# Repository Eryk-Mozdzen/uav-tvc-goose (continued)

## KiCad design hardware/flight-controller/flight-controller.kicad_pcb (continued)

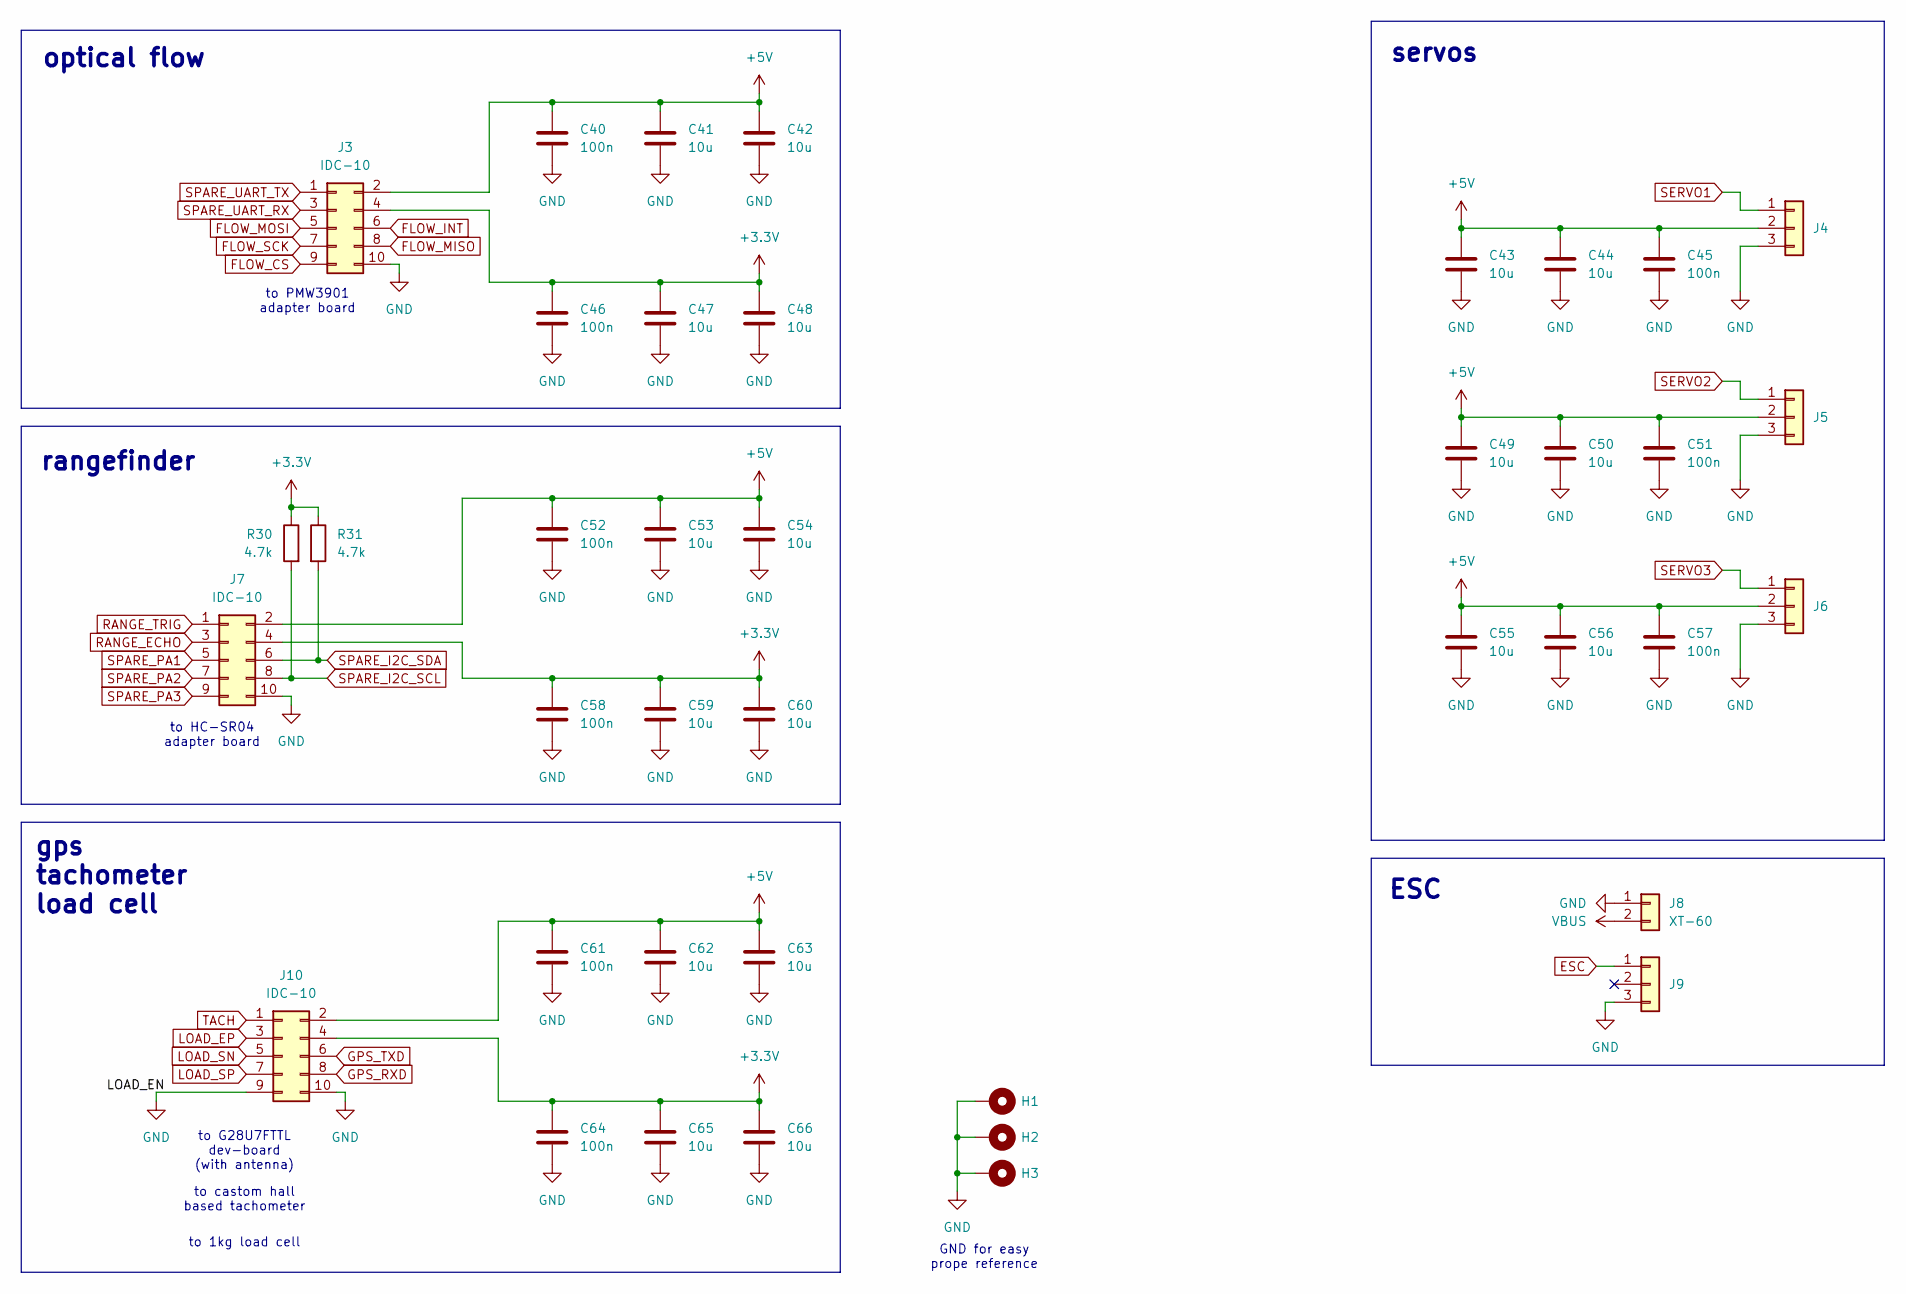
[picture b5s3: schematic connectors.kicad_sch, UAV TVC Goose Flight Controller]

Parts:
C40, C45, C46, C51, C52, C57, C58, C61, C64: 100n; C_0603_1608Metric
C41, C42, C43, C44, C47, C48, C49, C50, C53, C54, C55, C56, C59, C60, C62, C63, C65, C66: 10u; C_0603_1608Metric
H1, H2, H3: MountingHole_Pad; MountingHole_3.5mm_Pad_Via
J3, J7, J10: IDC-10; IDC-10-horizontal
J4, J5, J6, J9: Conn_01x03; header_1x3
J8: XT-60; XT60PW-F
R30, R31: 4.7k; R_0603_1608Metric

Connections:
+3.3V: C46.1, C47.1, C48.1, C58.1, C59.1, C60.1, C64.1, C65.1, C66.1, J3.4, J7.4, J10.4, R30.1, R31.1; also elsewhere on the board
+5V: C40.1, C41.1, C42.1, C43.1, C44.1, C45.1, C49.1, C50.1, C51.1, C52.1, C53.1, C54.1, C55.1, C56.1, C57.1, C61.1, C62.1, C63.1, J3.2, J4.2, J5.2, J6.2, J7.2, J10.2; also elsewhere on the board
ESC: J9.1; also elsewhere on the board
FLOW_CS: J3.9; also elsewhere on the board
FLOW_INT: J3.6; also elsewhere on the board
FLOW_MISO: J3.8; also elsewhere on the board
FLOW_MOSI: J3.5; also elsewhere on the board
FLOW_SCK: J3.7; also elsewhere on the board
GND: C40.2, C41.2, C42.2, C43.2, C44.2, C45.2, C46.2, C47.2, C48.2, C49.2, C50.2, C51.2, C52.2, C53.2, C54.2, C55.2, C56.2, C57.2, C58.2, C59.2, C60.2, C61.2, C62.2, C63.2, C64.2, C65.2, C66.2, H1.1, H2.1, H3.1, J3.10, J4.3, J5.3, J6.3, J7.10, J8.1, J9.3, J10.9, J10.10; also elsewhere on the board
GPS_RXD: J10.8; also elsewhere on the board
GPS_TXD: J10.6; also elsewhere on the board
LOAD_EP: J10.3; also elsewhere on the board
LOAD_SN: J10.5; also elsewhere on the board
LOAD_SP: J10.7; also elsewhere on the board
RANGE_ECHO: J7.3; also elsewhere on the board
RANGE_TRIG: J7.1; also elsewhere on the board
SERVO1: J4.1; also elsewhere on the board
SERVO2: J5.1; also elsewhere on the board
SERVO3: J6.1; also elsewhere on the board
SPARE_I2C_SCL: J7.8, R30.2; also elsewhere on the board
SPARE_I2C_SDA: J7.6, R31.2; also elsewhere on the board
SPARE_PA1: J7.5; also elsewhere on the board
SPARE_PA2: J7.7; also elsewhere on the board
SPARE_PA3: J7.9; also elsewhere on the board
SPARE_UART_RX: J3.3; also elsewhere on the board
SPARE_UART_TX: J3.1; also elsewhere on the board
TACH: J10.1; also elsewhere on the board
VBUS: J8.2; also elsewhere on the board

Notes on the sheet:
to HC-SR04 adapter board
to PMW3901 adapter board
to 1kg load cell
GND for easy prope reference
optical flow
ESC
to castom hall based tachometer
gps tachometer load cell
servos
rangefinder
to G28U7FTTL dev-board (with antenna)

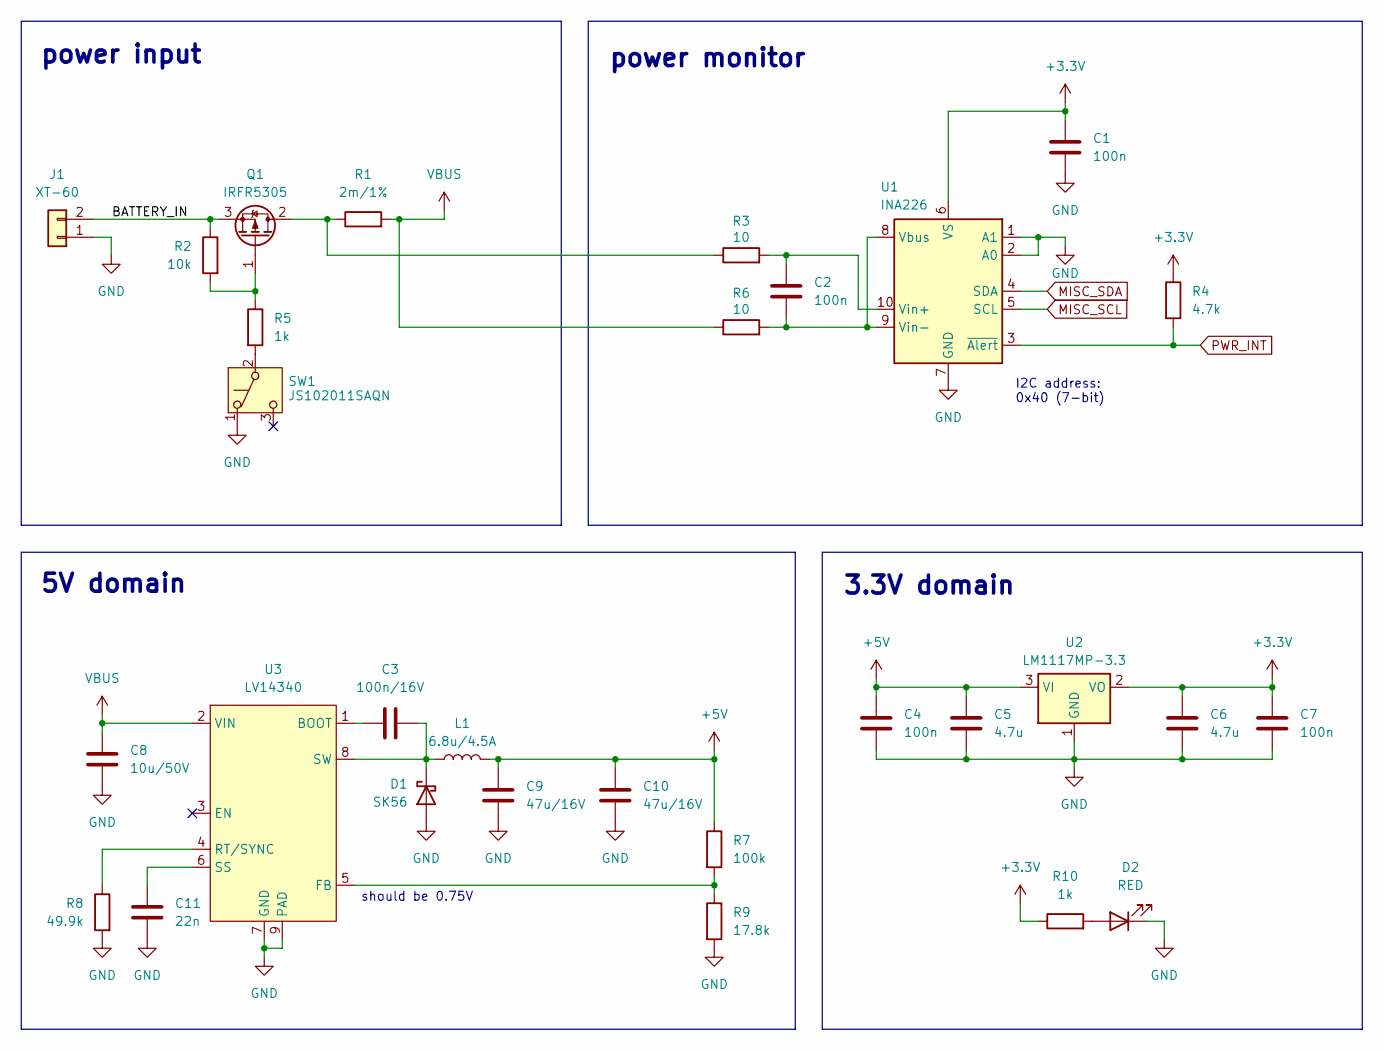
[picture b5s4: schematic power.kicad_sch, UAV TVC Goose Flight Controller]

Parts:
C1, C2, C4, C7: 100n; C_0603_1608Metric
C3: 100n/16V; C_0603_1608Metric
C5, C6: 4.7u; C_0603_1608Metric
C8: 10u/50V; C_1206_3216Metric
C9, C10: 47u/16V; C_1206_3216Metric
C11: 22n; C_0603_1608Metric
D1: SK56; D_SMB
D2: RED; LED_0603_1608Metric
J1: XT-60; XT60PW-M
L1: 6.8u/4.5A; PA4341.XXXNLT
Q1: IRFR5305; TO-252-2
R1: 2m/1%; R_1206_3216Metric
R2: 10k; R_0603_1608Metric
R3, R6: 10; R_0603_1608Metric
R4: 4.7k; R_0603_1608Metric
R5, R10: 1k; R_0603_1608Metric
R7: 100k; R_0603_1608Metric
R8: 49.9k; R_0603_1608Metric
R9: 17.8k; R_0603_1608Metric
SW1: JS102011SAQN
U1: INA226
U2: LM1117MP-3.3; LM1117-3.3
U3: LV14340

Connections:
+3.3V: C1.1, C6.1, C7.1, R4.1, R10.1, U1.6 (VS), U2.2 (VO); also elsewhere on the board
+5V: C4.1, C5.1, C9.1, C10.1, L1.2, R7.1, U2.3 (VI); also elsewhere on the board
/power/BATTERY_IN: J1.2, Q1.3 (S), R2.1
GND: C1.2, C4.2, C5.2, C6.2, C7.2, C8.2, C9.2, C10.2, C11.2, D1.2 (A), D2.1 (K), J1.1, R8.2, R9.2, SW1.1 (A), U1.1 (A1), U1.2 (A0), U1.7 (GND), U2.1 (GND), U3.7 (GND), U3.9 (PAD); also elsewhere on the board
MISC_SCL: U1.5 (SCL); also elsewhere on the board
MISC_SDA: U1.4 (SDA); also elsewhere on the board
unnamed: C3.2, D1.1 (K), L1.1, U3.8 (SW)
unnamed: D2.2 (A), R10.2
unnamed: Q1.2 (D), R1.1, R3.1
unnamed: Q1.1 (G), R2.2, R5.1
unnamed: R5.2, SW1.2 (B)
unnamed: C2.2, R6.2, U1.8 (Vbus), U1.9 (Vin-)
unnamed: C2.1, R3.2, U1.10 (Vin+)
unnamed: C3.1, U3.1 (BOOT)
unnamed: R7.2, R9.1, U3.5 (FB)
unnamed: R8.1, U3.4 (RT/SYNC)
unnamed: C11.1, U3.6 (SS)
PWR_INT: R4.2, U1.3 (~Alert); also elsewhere on the board
VBUS: C8.1, R1.2, R6.1, U3.2 (VIN); also elsewhere on the board

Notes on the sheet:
I2C address: 0x40 (7-bit)
5V domain
power monitor
should be 0.75V
3.3V domain
power input

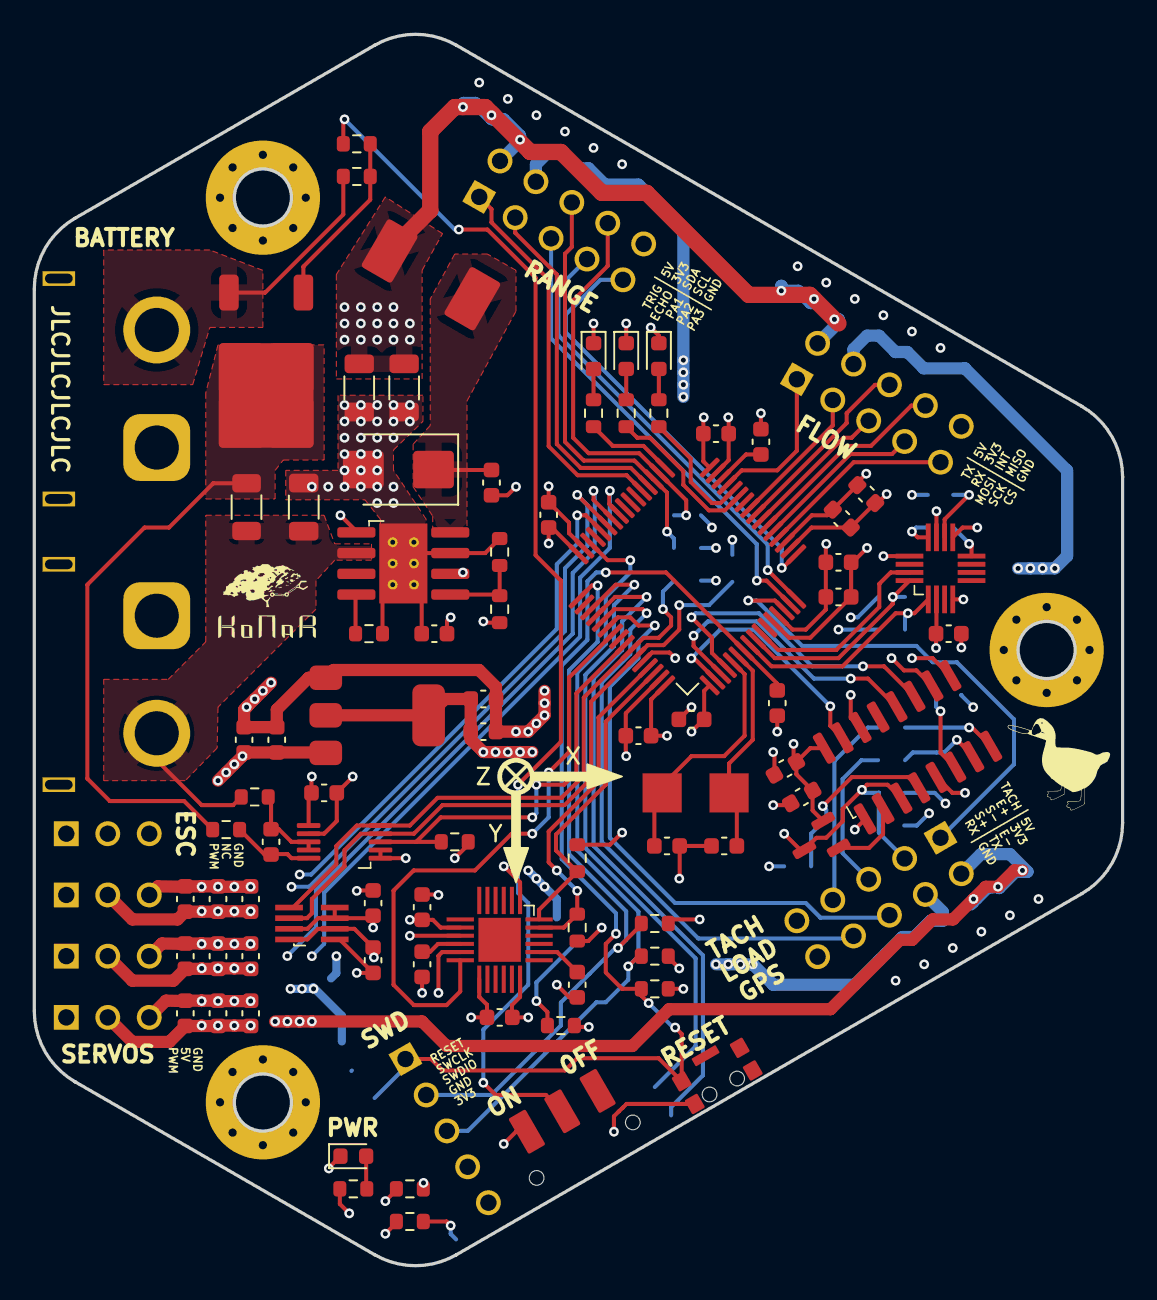
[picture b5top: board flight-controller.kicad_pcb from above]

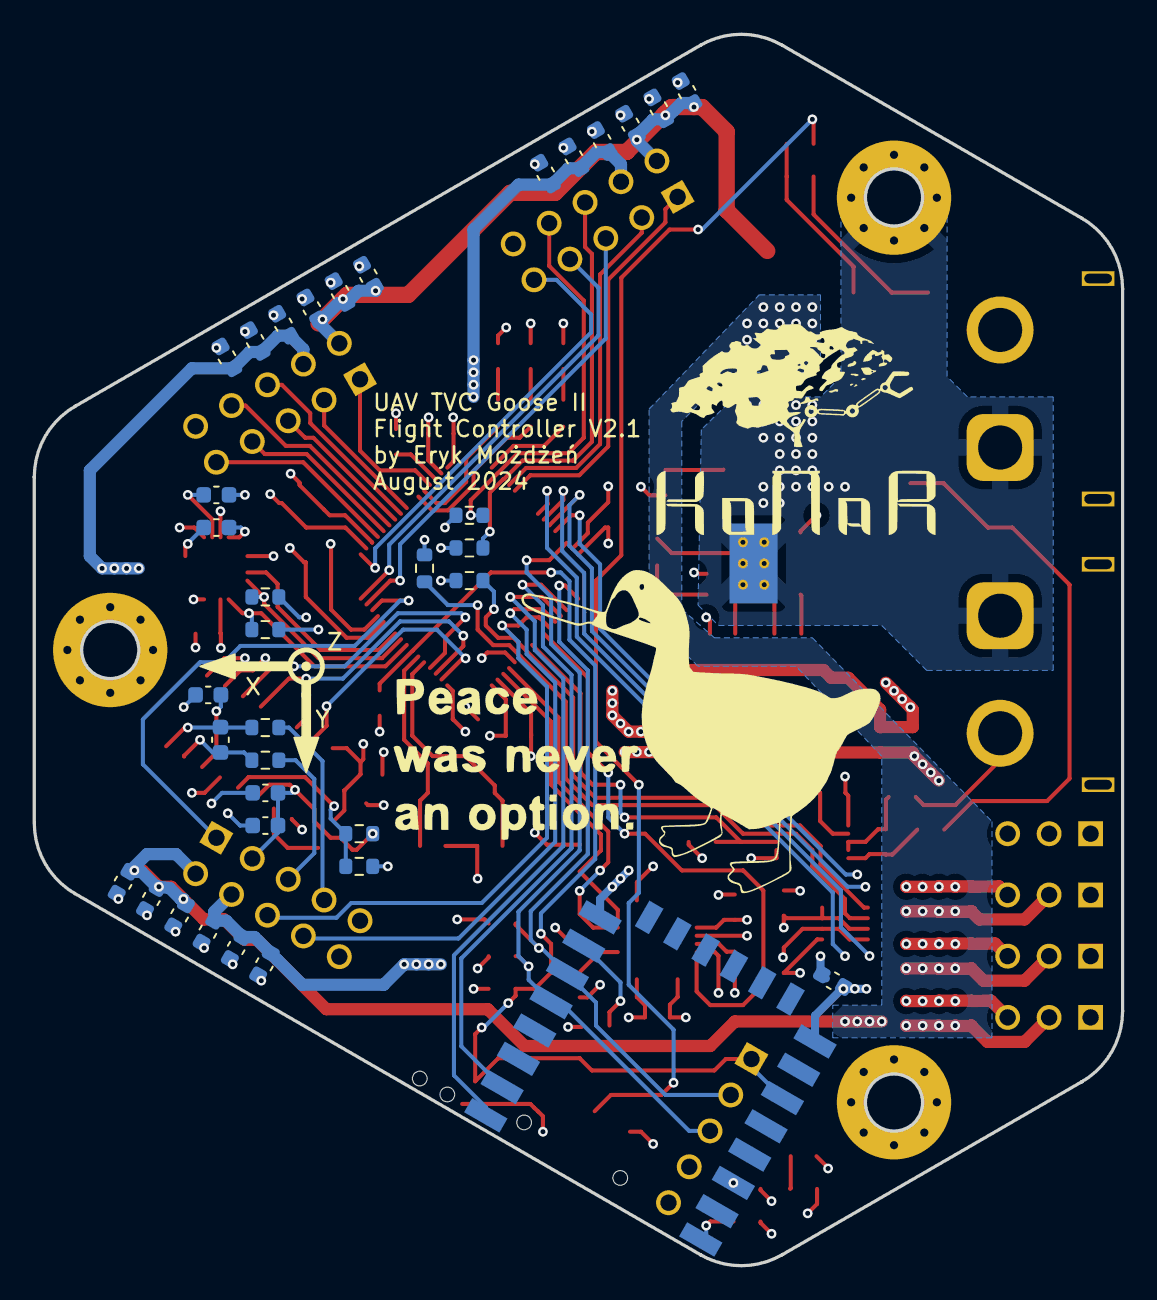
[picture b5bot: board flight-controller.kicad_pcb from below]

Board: 4 copper layers, 66.7 x 75.4 mm, 130 parts (36 on the bottom side), 79 nets.

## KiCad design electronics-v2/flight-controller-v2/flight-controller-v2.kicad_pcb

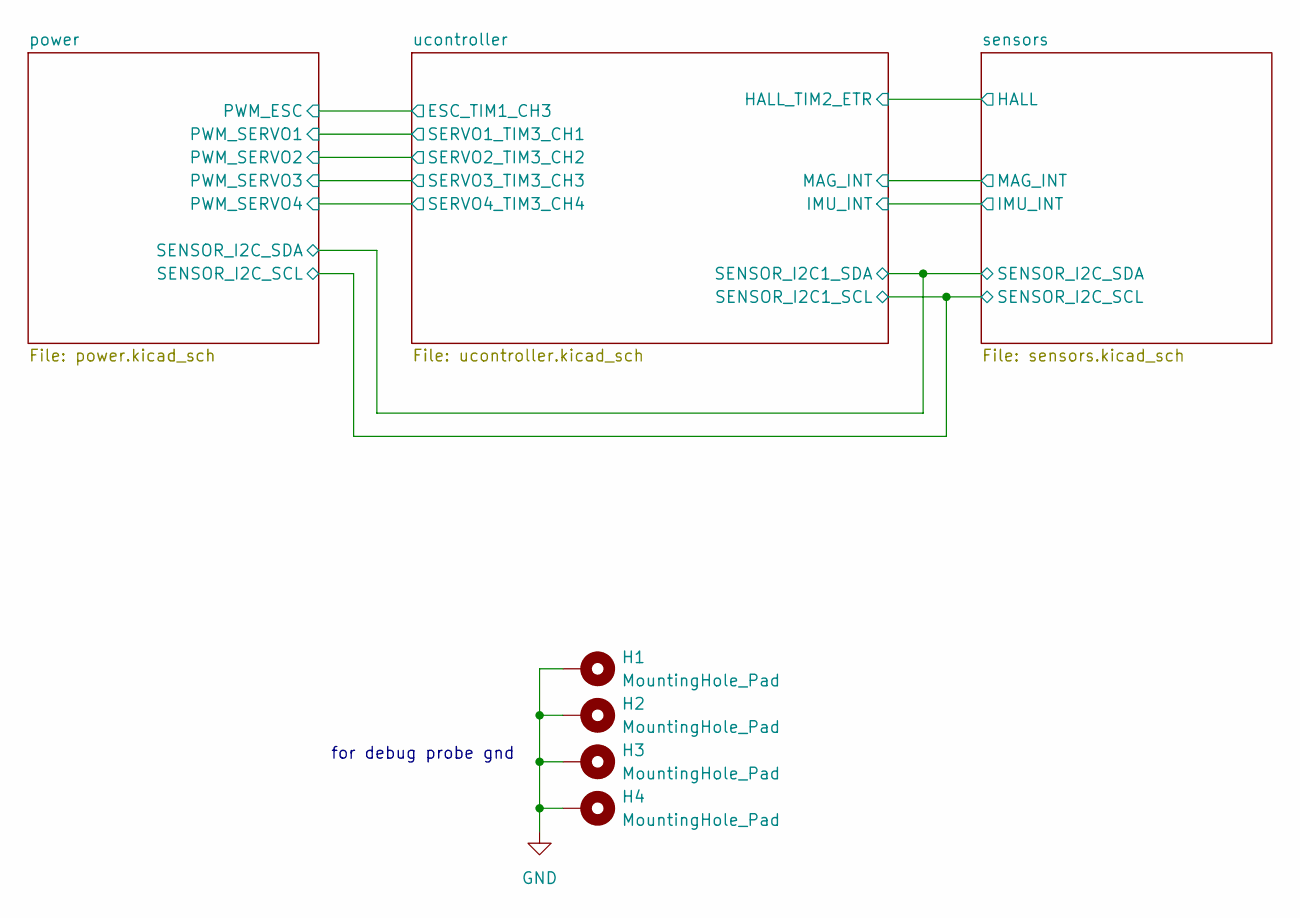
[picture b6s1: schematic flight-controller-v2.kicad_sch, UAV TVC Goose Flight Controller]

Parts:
H1, H2, H3, H4: MountingHole_Pad; MountingHole_3.2mm_M3_Pad_Via

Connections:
GND: H1.1, H2.1, H3.1, H4.1; also elsewhere on the board

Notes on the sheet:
for debug probe gnd

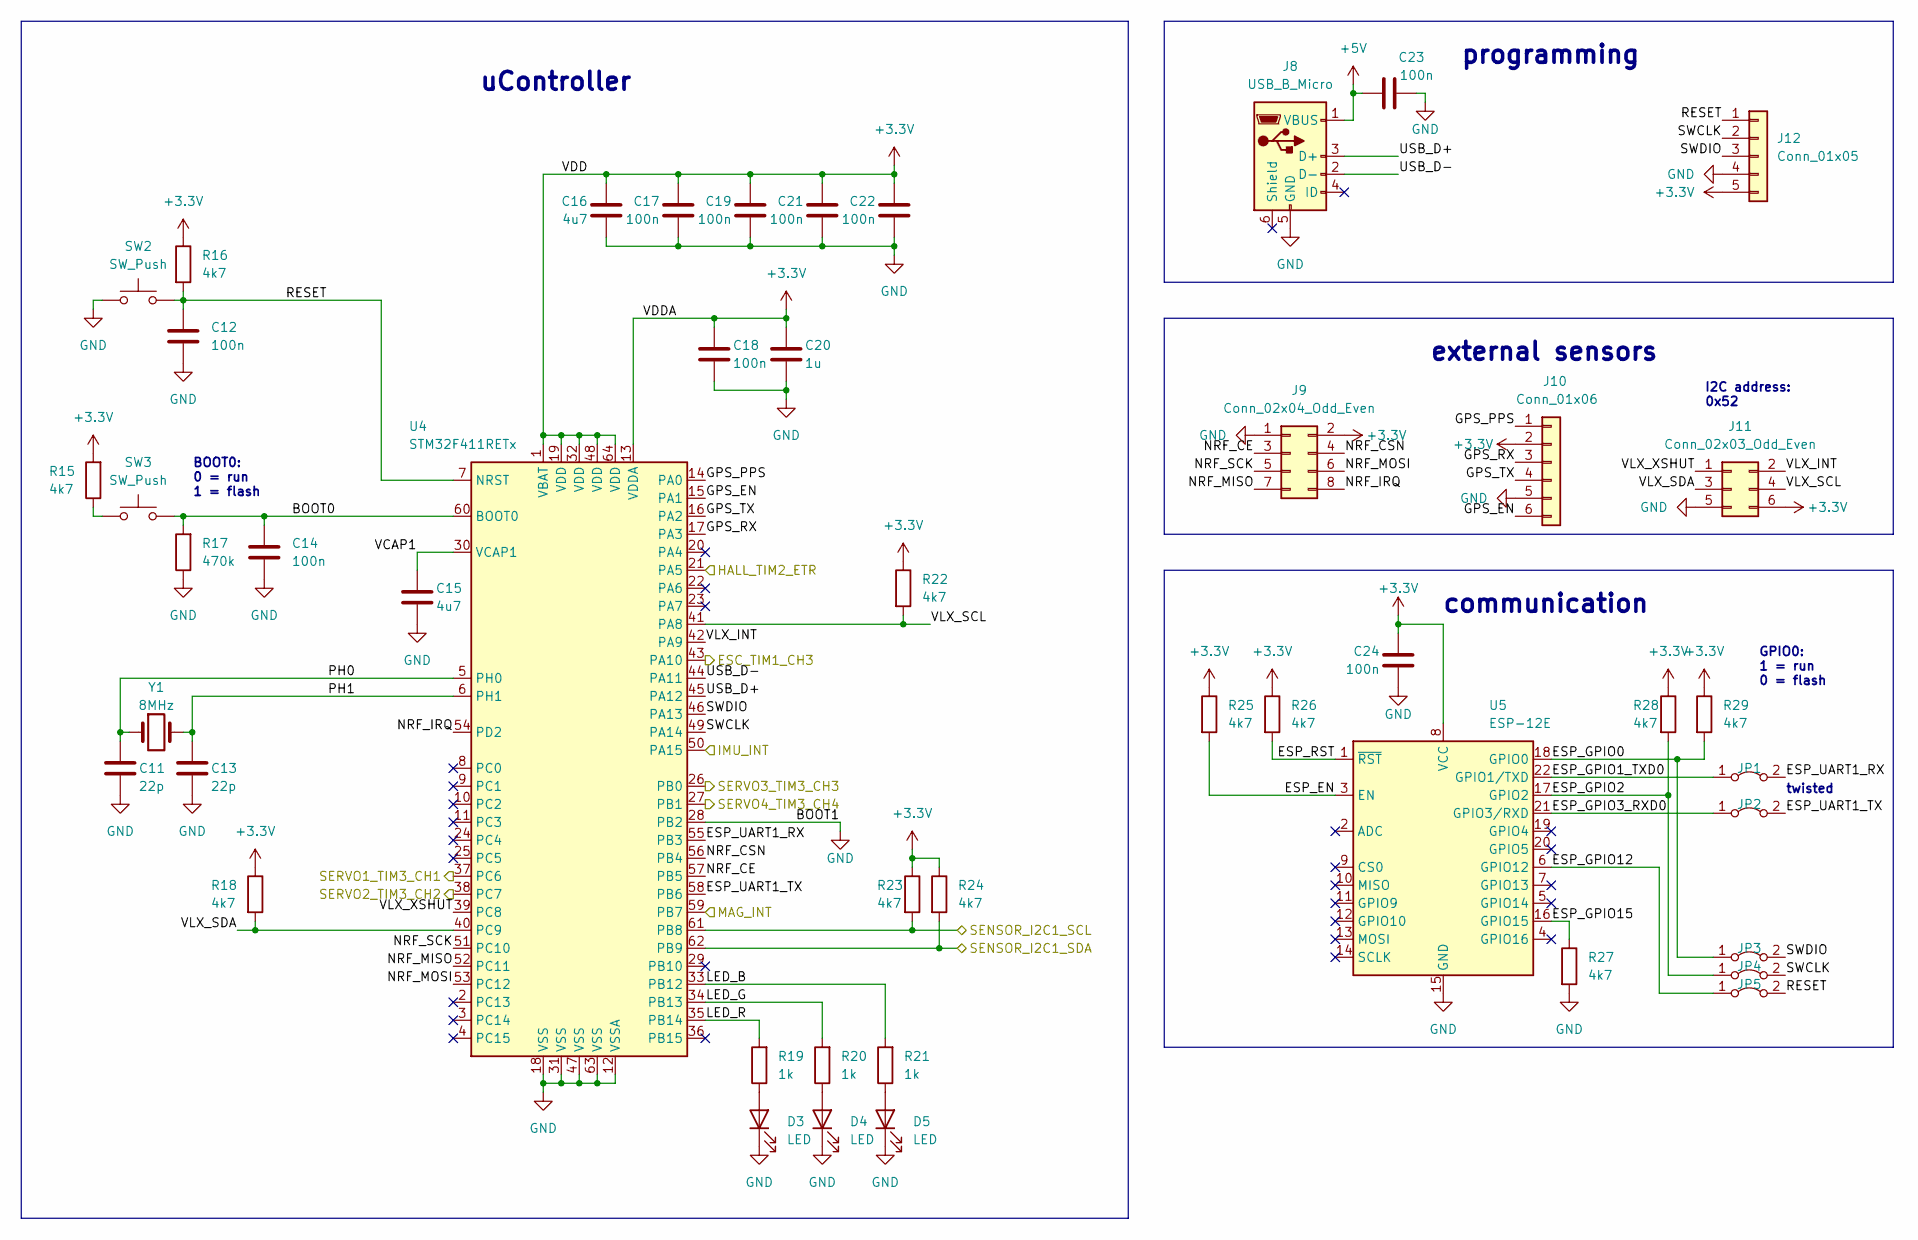
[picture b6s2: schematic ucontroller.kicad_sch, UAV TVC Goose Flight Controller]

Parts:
C11, C13: 22p; C_0603_1608Metric
C12, C14, C17, C18, C19, C21, C22, C23, C24: 100n; C_0603_1608Metric
C15, C16: 4u7; C_0603_1608Metric
C20: 1u; C_0603_1608Metric
D3, D4, D5: LED; LED_0603_1608Metric
J8: USB_B_Micro; usb_micro_B_druk_II
J9: Conn_02x04_Odd_Even; tht_pin_02x04
J10: Conn_01x06; tht_pin_01x06
J11: Conn_02x03_Odd_Even; IDC-Header_2x03_P2.54mm_Vertical
J12: Conn_01x05; tht_pin_01x05
JP1, JP2, JP3, JP4, JP5: SolderJumper-2_P1.3mm_Open_TrianglePad1.0x1.5mm
R15, R16, R18, R22, R23, R24, R25, R26, R27, R28, R29: 4k7; R_0603_1608Metric
R17: 470k; R_0603_1608Metric
R19, R20, R21: 1k; R_0603_1608Metric
SW2, SW3: SW_Push; SW_SPST_FSMSM
U4: STM32F411RETx; LQFP-64_10x10mm_P0.5mm
U5: ESP-12E
Y1: 8MHz; Crystal_SMD_5032-2Pin_5.0x3.2mm

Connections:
+3.3V: C16.1, C17.1, C18.1, C19.1, C20.1, C21.1, C22.1, C24.1, J9.2, J10.2, J11.6, J12.5, R15.2, R16.1, R18.1, R22.1, R23.1, R24.1, R25.1, R26.1, R28.1, R29.1, U4.1 (VBAT), U4.13 (VDDA), U4.19 (VDD), U4.32 (VDD), U4.48 (VDD), U4.64 (VDD), U5.8 (VCC); also elsewhere on the board
+5V: C23.1, J8.1 (VBUS); also elsewhere on the board
/power/PWM_ESC: U4.43 (PA10); also elsewhere on the board
/power/PWM_SERVO1: U4.37 (PC6); also elsewhere on the board
/power/PWM_SERVO2: U4.38 (PC7); also elsewhere on the board
/power/PWM_SERVO3: U4.26 (PB0); also elsewhere on the board
/power/PWM_SERVO4: U4.27 (PB1); also elsewhere on the board
/power/SENSOR_I2C_SCL: R23.2, U4.61 (PB8); also elsewhere on the board
/power/SENSOR_I2C_SDA: R24.2, U4.62 (PB9); also elsewhere on the board
/sensors/HALL: U4.21 (PA5); also elsewhere on the board
/sensors/IMU_INT: U4.50 (PA15); also elsewhere on the board
/sensors/MAG_INT: U4.59 (PB7); also elsewhere on the board
/ucontroller/BOOT0: C14.1, R17.2, SW3.2, U4.60 (BOOT0)
/ucontroller/ESP_EN: R25.2, U5.3 (EN)
/ucontroller/ESP_GPIO0: JP3.1 (A), R29.2, U5.18 (GPIO0)
/ucontroller/ESP_GPIO1_TXD0: JP1.1 (A), U5.22 (GPIO1/TXD)
/ucontroller/ESP_GPIO2: JP4.1 (A), R28.2, U5.17 (GPIO2)
/ucontroller/ESP_GPIO3_RXD0: JP2.1 (A), U5.21 (GPIO3/RXD)
/ucontroller/ESP_GPIO12: JP5.1 (A), U5.6 (GPIO12)
/ucontroller/ESP_GPIO15: R27.1, U5.16 (GPIO15)
/ucontroller/ESP_RST: R26.2, U5.1 (~RST)
/ucontroller/ESP_UART1_RX: JP1.2 (B), U4.55 (PB3)
/ucontroller/ESP_UART1_TX: JP2.2 (B), U4.58 (PB6)
/ucontroller/GPS_EN: J10.6, U4.15 (PA1)
/ucontroller/GPS_PPS: J10.1, U4.14 (PA0)
/ucontroller/GPS_RX: J10.3, U4.17 (PA3)
/ucontroller/GPS_TX: J10.4, U4.16 (PA2)
/ucontroller/LED_B: R21.2, U4.33 (PB12)
/ucontroller/LED_G: R20.2, U4.34 (PB13)
/ucontroller/LED_R: R19.2, U4.35 (PB14)
/ucontroller/NRF_CE: J9.3, U4.57 (PB5)
/ucontroller/NRF_CSN: J9.4, U4.56 (PB4)
/ucontroller/NRF_IRQ: J9.8, U4.54 (PD2)
/ucontroller/NRF_MISO: J9.7, U4.52 (PC11)
/ucontroller/NRF_MOSI: J9.6, U4.53 (PC12)
/ucontroller/NRF_SCK: J9.5, U4.51 (PC10)
/ucontroller/PH0: C11.1, U4.5 (PH0), Y1.1
/ucontroller/PH1: C13.1, U4.6 (PH1), Y1.2
/ucontroller/RESET: C12.1, J12.1, JP5.2 (B), R16.2, SW2.2, U4.7 (NRST)
/ucontroller/SWCLK: J12.2, JP4.2 (B), U4.49 (PA14)
/ucontroller/SWDIO: J12.3, JP3.2 (B), U4.46 (PA13)
/ucontroller/USB_D+: J8.3 (D+), U4.45 (PA12)
/ucontroller/USB_D-: J8.2 (D-), U4.44 (PA11)
/ucontroller/VCAP1: C15.1, U4.30 (VCAP1)
/ucontroller/VLX_INT: J11.2, U4.42 (PA9)
/ucontroller/VLX_SCL: J11.4, R22.2, U4.41 (PA8)
/ucontroller/VLX_SDA: J11.3, R18.2, U4.40 (PC9)
/ucontroller/VLX_XSHUT: J11.1, U4.39 (PC8)
GND: C11.2, C12.2, C13.2, C14.2, C15.2, C16.2, C17.2, C18.2, C19.2, C20.2, C21.2, C22.2, C23.2, C24.2, D3.1 (K), D4.1 (K), D5.1 (K), J8.5 (GND), J9.1, J10.5, J11.5, J12.4, R17.1, R27.2, SW2.1, U4.12 (VSSA), U4.18 (VSS), U4.28 (PB2), U4.31 (VSS), U4.47 (VSS), U4.63 (VSS), U5.15 (GND); also elsewhere on the board
unnamed: D3.2 (A), R19.1
unnamed: D4.2 (A), R20.1
unnamed: D5.2 (A), R21.1
unnamed: R15.1, SW3.1

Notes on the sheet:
BOOT0: 0 = run 1 = flash
programming
I2C address: 0x52
GPIO0: 1 = run 0 = flash
external sensors
communication
uController
twisted

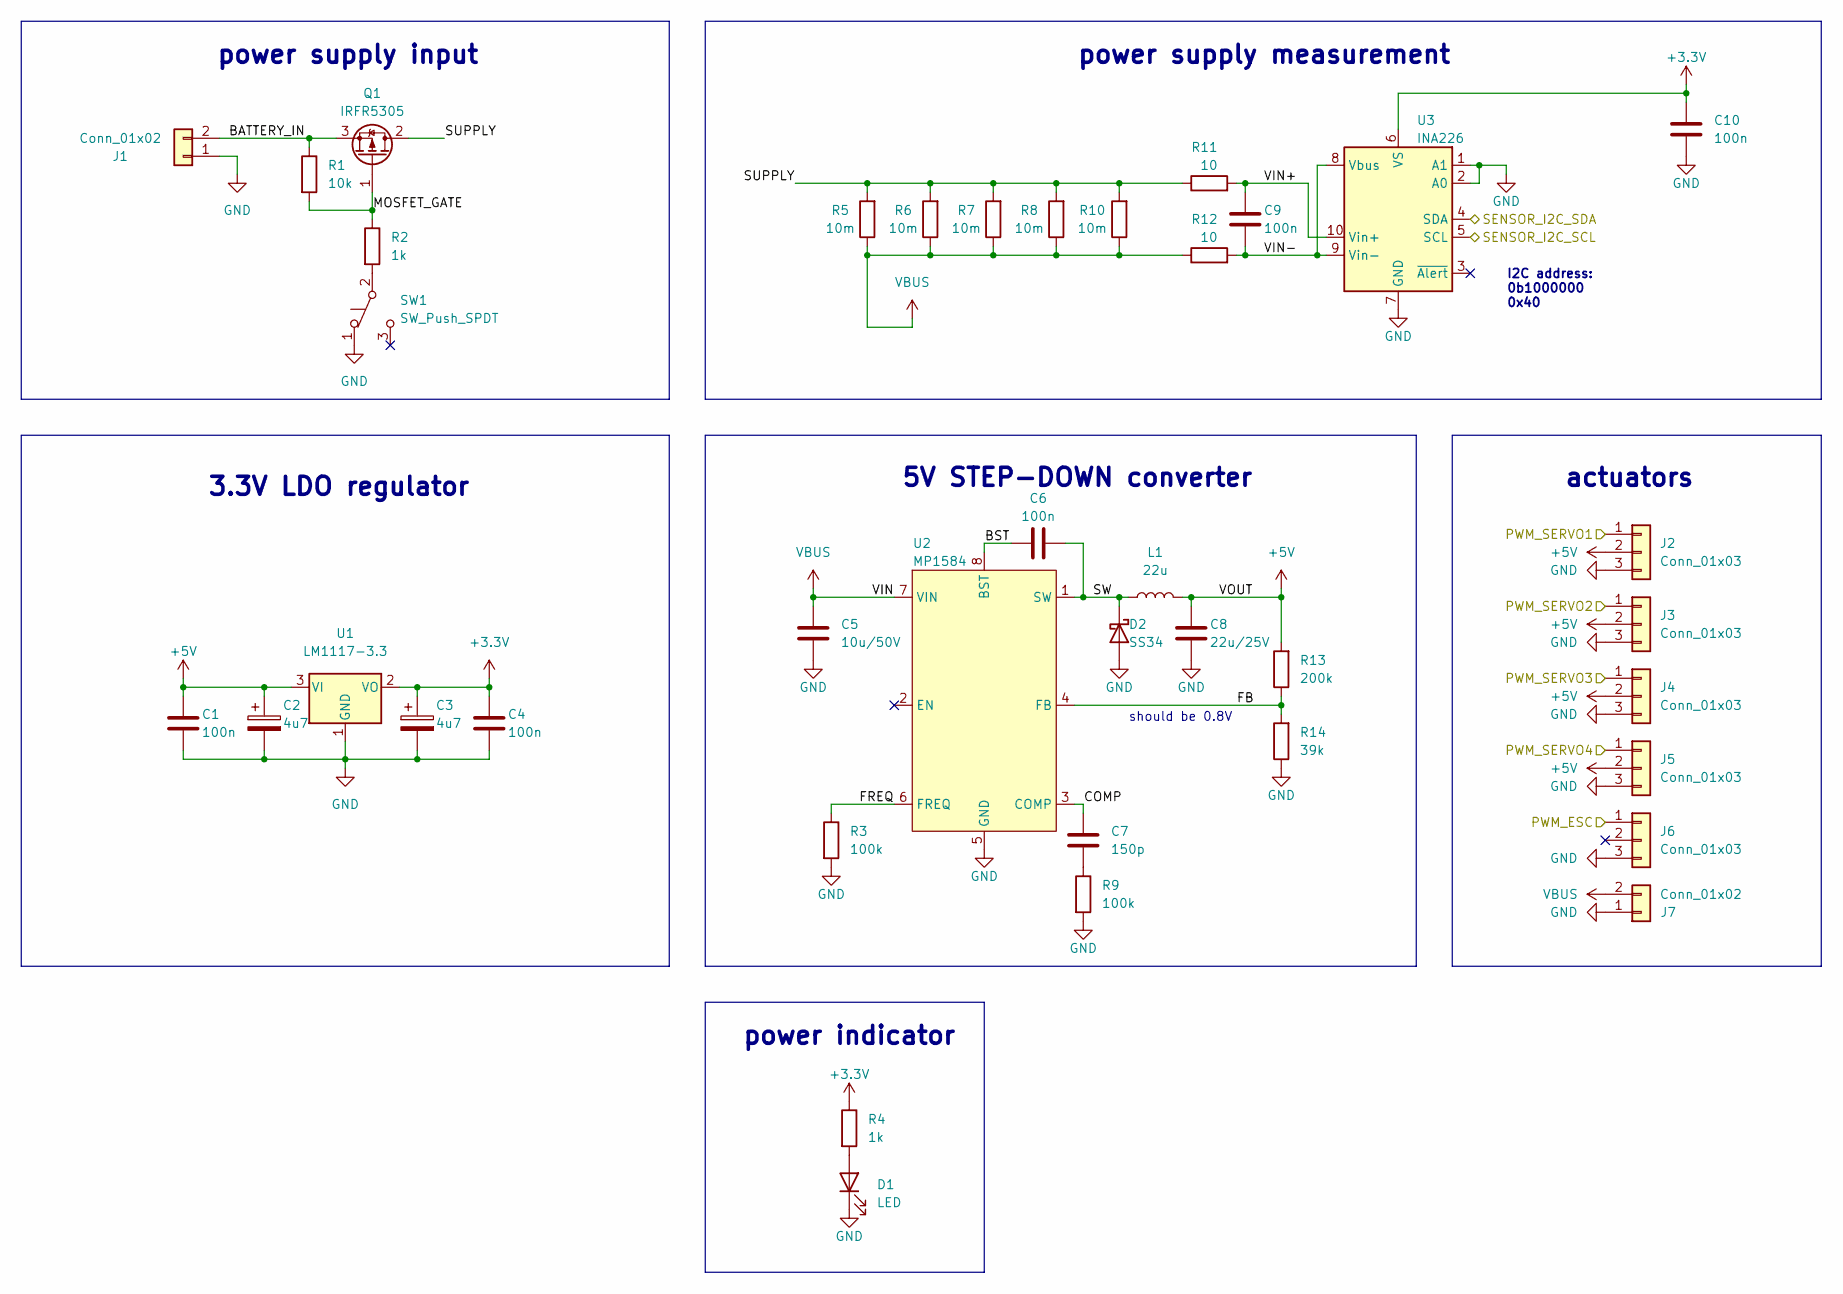
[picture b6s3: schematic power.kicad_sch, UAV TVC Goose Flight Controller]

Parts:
C1, C4, C6, C9, C10: 100n; C_0603_1608Metric
C2, C3: 4u7; CP_EIA-3216-18_Kemet-A
C5: 10u/50V; C_1206_3216Metric
C7: 150p; C_0603_1608Metric
C8: 22u/25V; C_1206_3216Metric
D1: LED; LED_0603_1608Metric
D2: SS34; D_SMA
J1: Conn_01x02; AMASS_XT60-M_1x02_P7.20mm_Vertical
J2, J3, J4, J5, J6: Conn_01x03; PinHeader_1x03_P2.54mm_Vertical
J7: Conn_01x02; AMASS_XT60-F_1x02_P7.20mm_Vertical
L1: 22u; L_AVX_LMLP07A7
Q1: IRFR5305; TO-252-2
R1: 10k; R_0603_1608Metric
R2, R4: 1k; R_0603_1608Metric
R3, R9: 100k; R_0603_1608Metric
R5, R6, R7, R8, R10: 10m; R_1206_3216Metric
R11, R12: 10; R_0603_1608Metric
R13: 200k; R_0603_1608Metric
R14: 39k; R_0603_1608Metric
SW1: SW_Push_SPDT; SW_CuK_JS202011CQN_DPDT_Straight
U1: LM1117-3.3; SOT-223-3_TabPin2
U2: MP1584; SOIC-8-1EP_3.9x4.9mm_P1.27mm_EP2.62x3.51mm_ThermalVias
U3: INA226; VSSOP-10_3x3mm_P0.5mm

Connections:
+3.3V: C3.1, C4.1, C10.2, R4.1, U1.2 (VO), U3.6 (VS); also elsewhere on the board
+5V: C1.1, C2.1, C8.2, J2.2, J3.2, J4.2, J5.2, L1.2, R13.2, U1.3 (VI); also elsewhere on the board
/power/BATTERY_IN: J1.2, Q1.3 (S), R1.1
/power/BST: C6.1, U2.8 (BST)
/power/COMP: C7.1, U2.3 (COMP)
/power/FB: R13.1, R14.2, U2.4 (FB)
/power/FREQ: R3.1, U2.6 (FREQ)
/power/MOSFET_GATE: Q1.1 (G), R1.2, R2.1
/power/PWM_ESC: J6.1; also elsewhere on the board
/power/PWM_SERVO1: J2.1; also elsewhere on the board
/power/PWM_SERVO2: J3.1; also elsewhere on the board
/power/PWM_SERVO3: J4.1; also elsewhere on the board
/power/PWM_SERVO4: J5.1; also elsewhere on the board
/power/SENSOR_I2C_SCL: U3.5 (SCL); also elsewhere on the board
/power/SENSOR_I2C_SDA: U3.4 (SDA); also elsewhere on the board
/power/SUPPLY: Q1.2 (D), R5.2, R6.2, R7.2, R8.2, R10.2, R11.1
/power/SW: C6.2, D2.1 (K), L1.1, U2.1 (SW)
/power/VIN+: C9.2, R11.2, U3.10 (Vin+)
/power/VIN-: C9.1, R12.2, U3.8 (Vbus), U3.9 (Vin-)
GND: C1.2, C2.2, C3.2, C4.2, C5.1, C8.1, C10.1, D1.1 (K), D2.2 (A), J1.1, J2.3, J3.3, J4.3, J5.3, J6.3, J7.1, R3.2, R9.2, R14.1, SW1.1 (A), U1.1 (GND), U2.5 (GND), U3.1 (A1), U3.2 (A0), U3.7 (GND); also elsewhere on the board
unnamed: C7.2, R9.1
unnamed: D1.2 (A), R4.2
unnamed: R2.2, SW1.2 (B)
VBUS: C5.2, J7.2, R5.1, R6.1, R7.1, R8.1, R10.1, R12.1, U2.7 (VIN)

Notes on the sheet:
power indicator
I2C address: 0b1000000 0x40
5V STEP-DOWN converter
3.3V LDO regulator
should be 0.8V
power supply input
power supply measurement
actuators

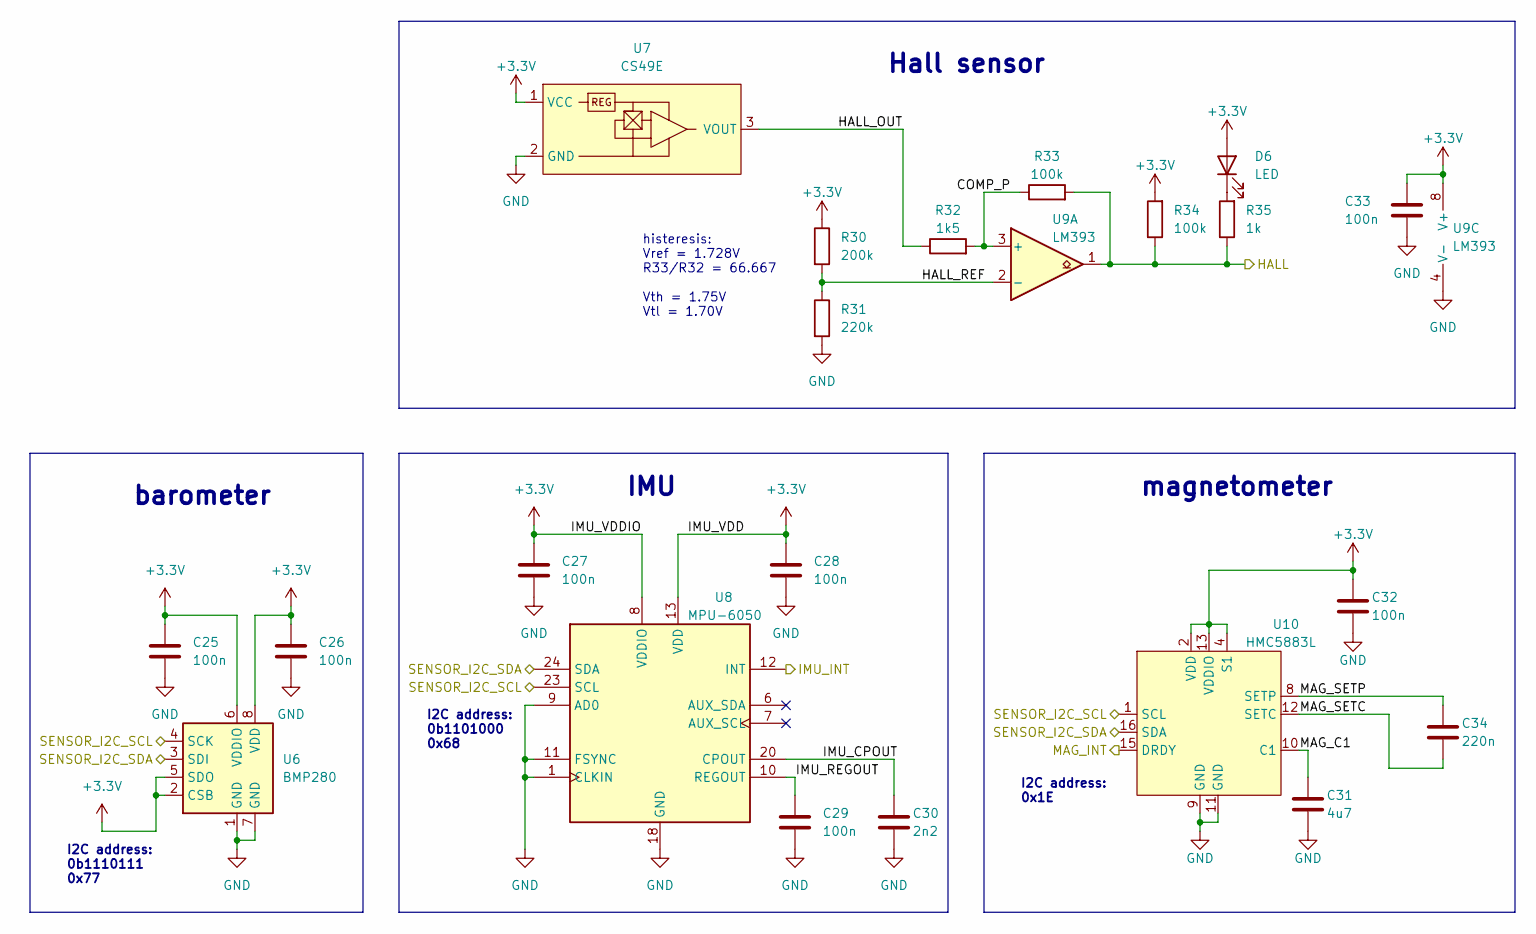
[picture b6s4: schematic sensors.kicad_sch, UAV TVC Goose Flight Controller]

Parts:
C25, C26, C27, C28, C29, C32, C33: 100n; C_0603_1608Metric
C30: 2n2; C_0603_1608Metric
C31: 4u7; C_0603_1608Metric
C34: 220n; C_0603_1608Metric
D6: LED; LED_0603_1608Metric
R30: 200k; R_0603_1608Metric
R31: 220k; R_0603_1608Metric
R32: 1k5; R_0603_1608Metric
R33, R34: 100k; R_0603_1608Metric
R35: 1k; R_0603_1608Metric
U6: BMP280; bmp280_hand_solder
U7: CS49E; tht_pin_01x03
U8: MPU-6050; mpu6050_hand_solder
U9: LM393; SOIC-8_3.9x4.9mm_P1.27mm
U10: HMC5883L; qmc5883l_hand_solder

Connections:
+3.3V: C25.1, C26.1, C27.1, C28.1, C32.1, C33.1, D6.2 (A), R30.1, R34.2, U6.2 (CSB), U6.5 (SDO), U6.6 (VDDIO), U6.8 (VDD), U7.1 (VCC), U8.8 (VDDIO), U8.13 (VDD), U9.8 (V+), U10.2 (VDD), U10.4 (S1), U10.13 (VDDIO); also elsewhere on the board
/power/SENSOR_I2C_SCL: U6.4 (SCK), U8.23 (SCL), U10.1 (SCL); also elsewhere on the board
/power/SENSOR_I2C_SDA: U6.3 (SDI), U8.24 (SDA), U10.16 (SDA); also elsewhere on the board
/sensors/COMP_P: R32.2, R33.1, U9.3 (+)
/sensors/HALL: R33.2, R34.1, R35.1, U9.1; also elsewhere on the board
/sensors/HALL_OUT: R32.1, U7.3 (VOUT)
/sensors/HALL_REF: R30.2, R31.1, U9.2 (-)
/sensors/IMU_CPOUT: C30.1, U8.20 (CPOUT)
/sensors/IMU_INT: U8.12 (INT); also elsewhere on the board
/sensors/IMU_REGOUT: C29.1, U8.10 (REGOUT)
/sensors/MAG_C1: C31.1, U10.10 (C1)
/sensors/MAG_INT: U10.15 (DRDY); also elsewhere on the board
/sensors/MAG_SETC: C34.2, U10.12 (SETC)
/sensors/MAG_SETP: C34.1, U10.8 (SETP)
GND: C25.2, C26.2, C27.2, C28.2, C29.2, C30.2, C31.2, C32.2, C33.2, R31.2, U6.1 (GND), U6.7 (GND), U7.2 (GND), U8.1 (CLKIN), U8.9 (AD0), U8.11 (FSYNC), U8.18 (GND), U9.4 (V-), U10.9 (GND), U10.11 (GND); also elsewhere on the board
unnamed: D6.1 (K), R35.2

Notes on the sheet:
I2C address: 0b1110111 0x77
magnetometer
histeresis: Vref = 1.728V R33/R32 = 66.667 Vth = 1.75V Vtl = 1.70V
I2C address: 0x1E
I2C address: 0b1101000 0x68
Hall sensor
barometer
IMU
